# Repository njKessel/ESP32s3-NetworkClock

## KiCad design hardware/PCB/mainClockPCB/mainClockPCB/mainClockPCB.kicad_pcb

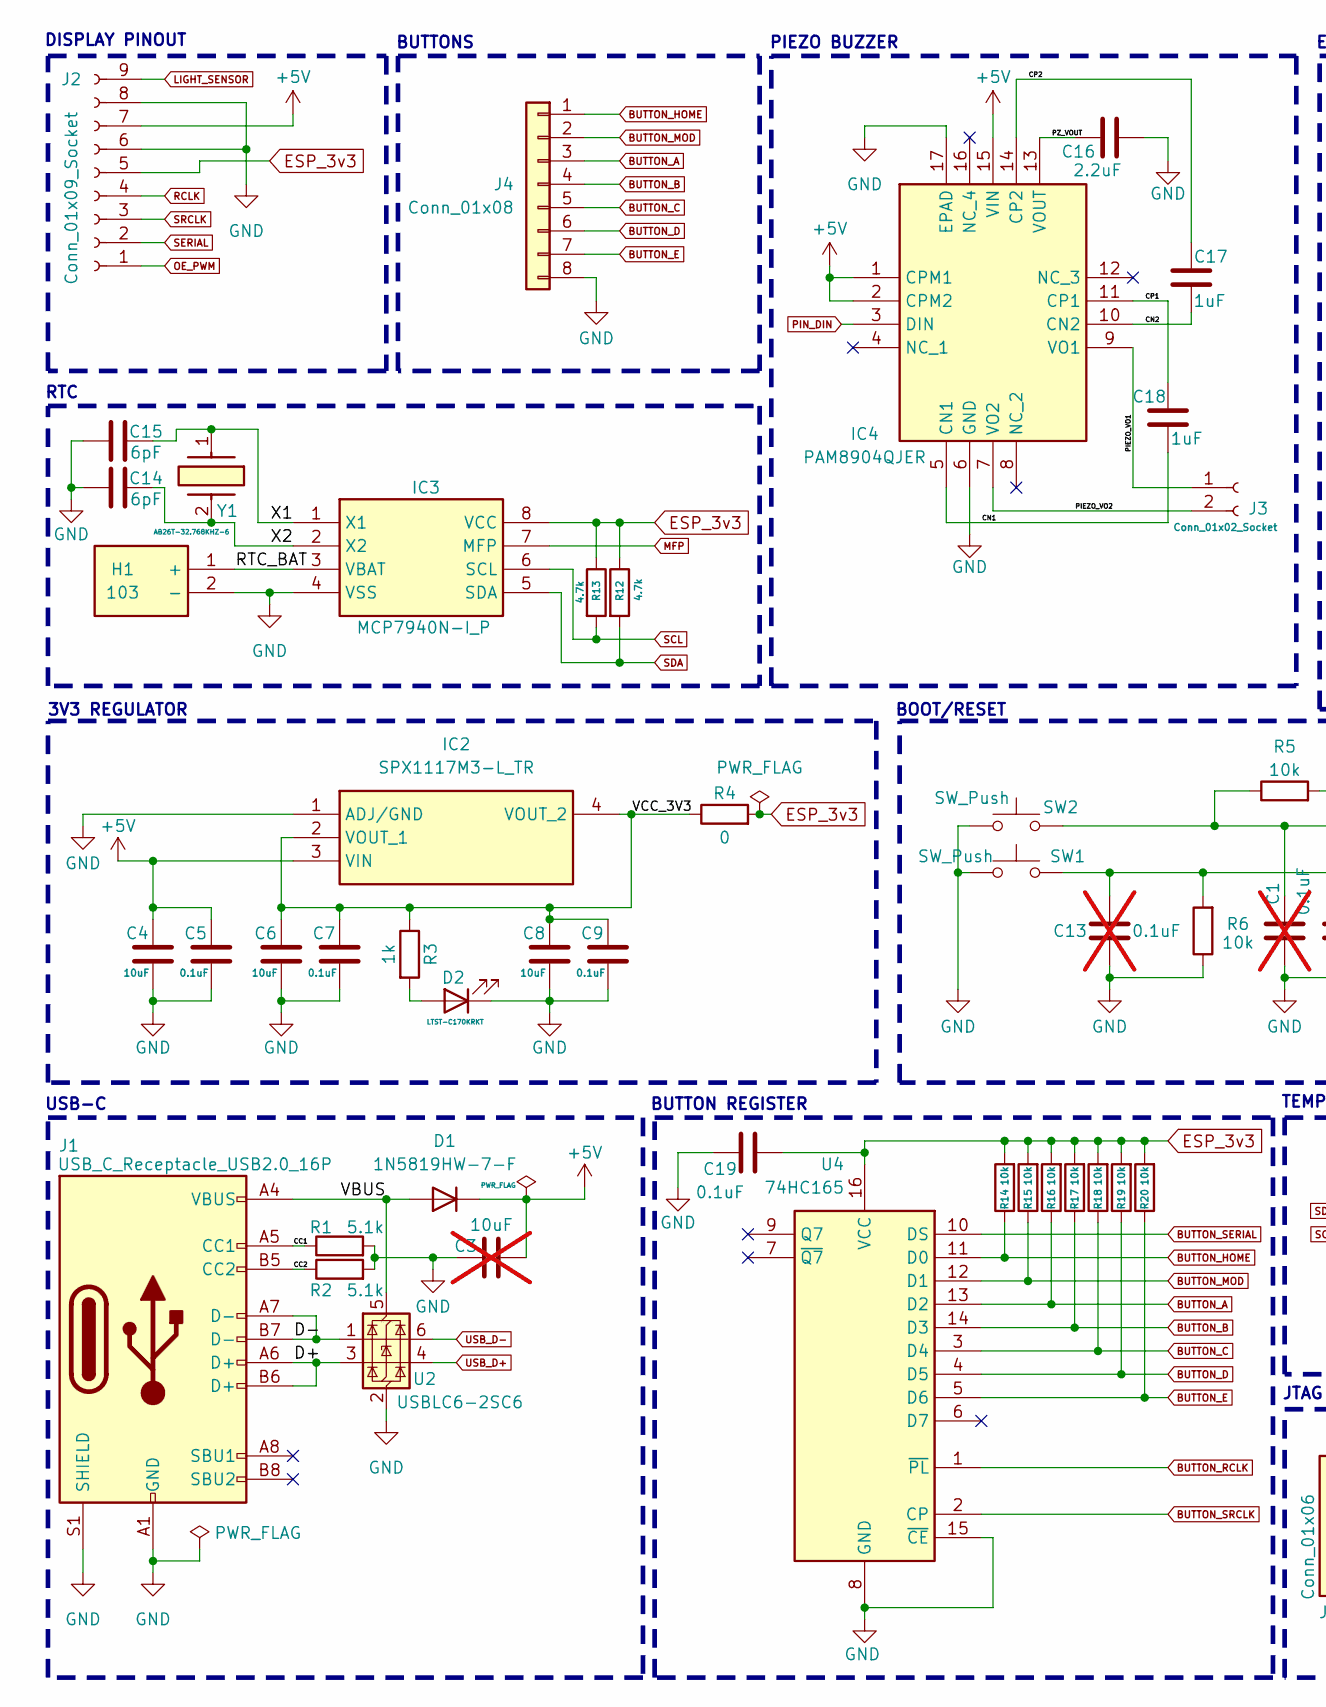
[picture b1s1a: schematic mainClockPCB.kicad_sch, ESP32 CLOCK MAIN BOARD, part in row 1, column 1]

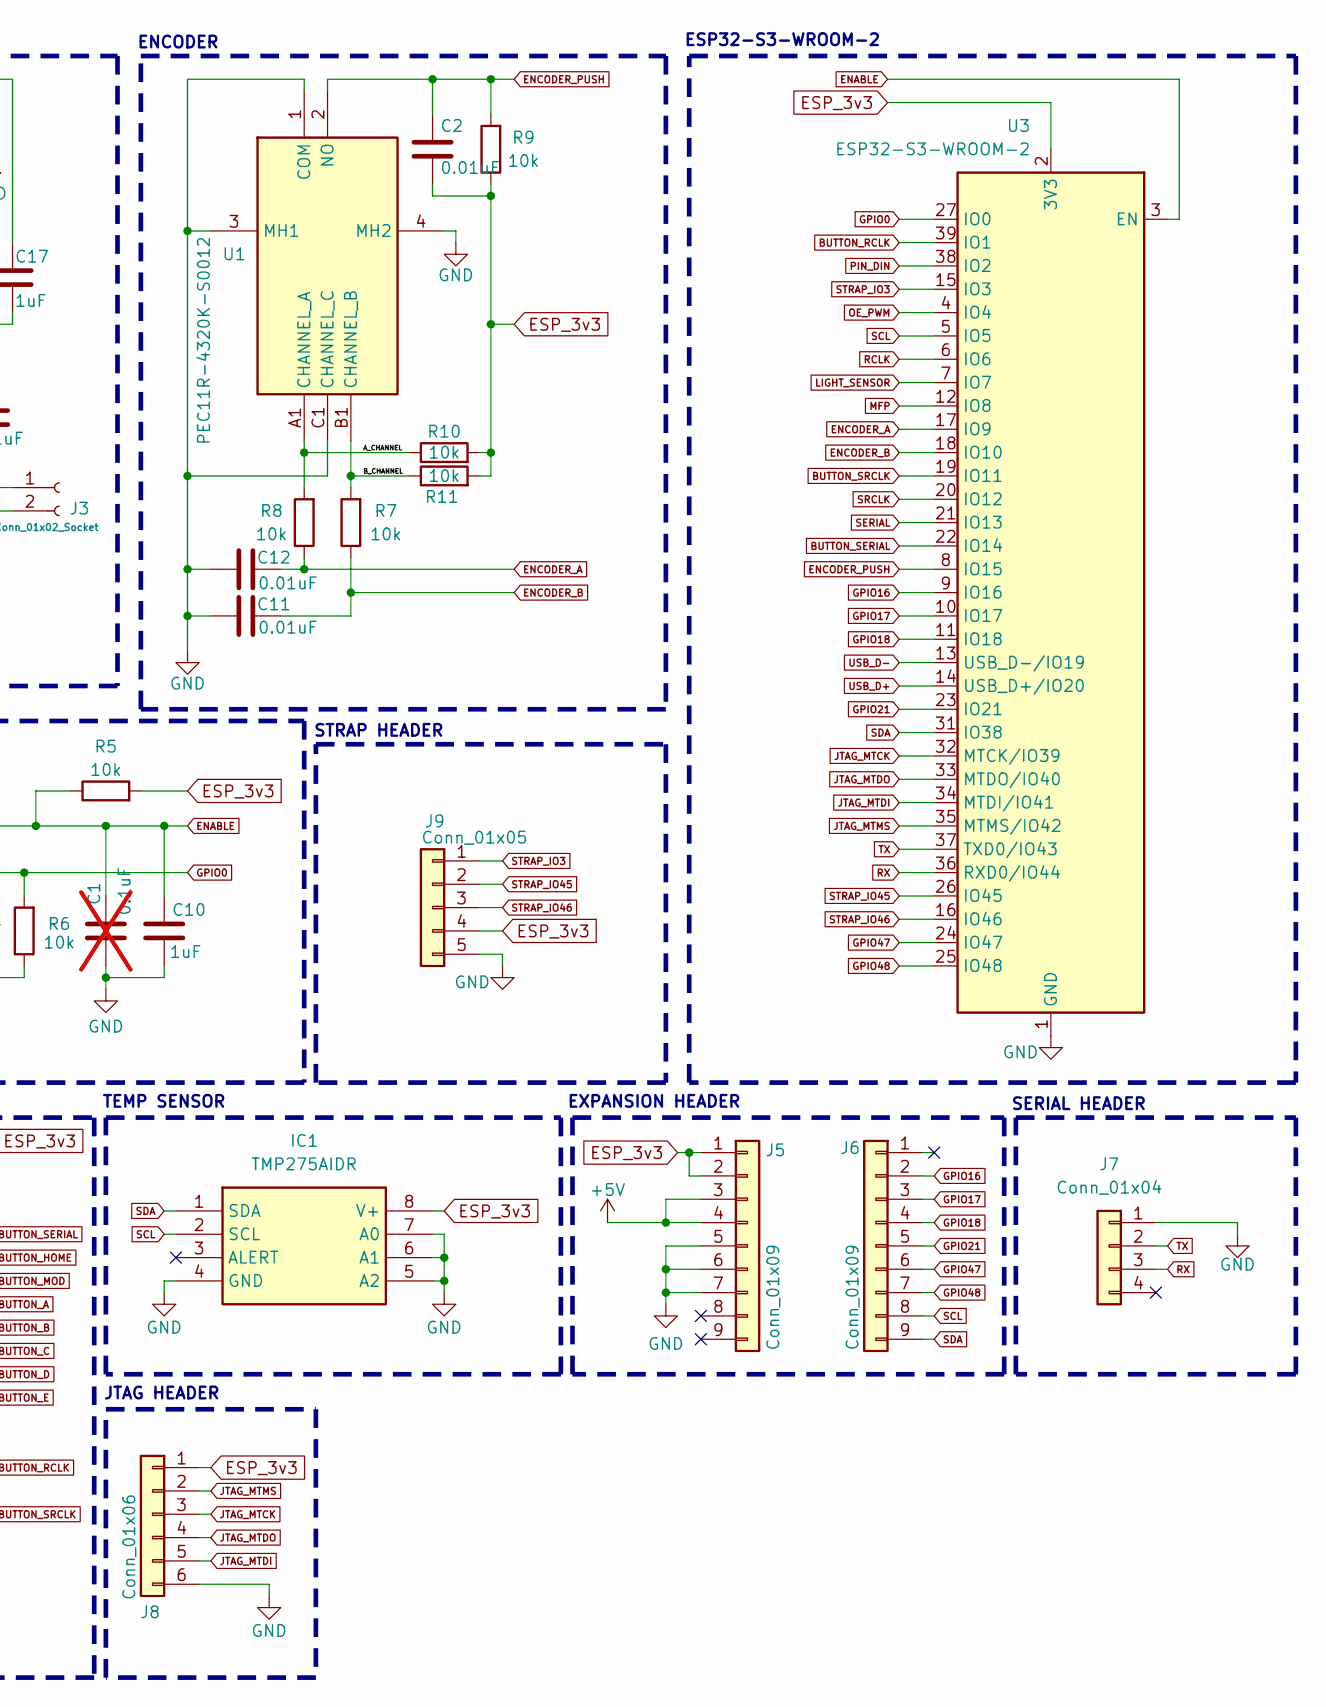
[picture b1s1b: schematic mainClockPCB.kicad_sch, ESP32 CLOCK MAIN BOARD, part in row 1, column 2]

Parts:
C1, C13: 0.1uF; C_0603_1608Metric_Pad1.08x0.95mm_HandSolder; Voltage 50V; Tolerance 10%; not fitted
C2, C11, C12: 0.01uF; C_0603_1608Metric_Pad1.08x0.95mm_HandSolder
C3: 10uF; C_0805_2012Metric_Pad1.18x1.45mm_HandSolder; not fitted
C4, C6, C8: 10uF; C_0805_2012Metric_Pad1.18x1.45mm_HandSolder
C5, C7, C9, C19: 0.1uF; C_0603_1608Metric_Pad1.08x0.95mm_HandSolder
C10, C17, C18: 1uF; C_0603_1608Metric_Pad1.08x0.95mm_HandSolder
C14, C15: 6pF; C_0603_1608Metric_Pad1.08x0.95mm_HandSolder
C16: 2.2uF; C_0603_1608Metric_Pad1.08x0.95mm_HandSolder
D1: 1N5819HW-7-F; D_SOD-123
D2: LTST-C170KRKT; LED_0805_2012Metric_Pad1.15x1.40mm_HandSolder
H1: 103; Manufacturer_Part_Number 103; Mouser Part Number 534-103
IC1: TMP275AIDR; SOIC127P600X175-8N; Manufacturer_Part_Number TMP275AIDR; Mouser Part Number 595-TMP275AIDR
IC2: SPX1117M3-L_TR; SOT230P700X180-4N; Manufacturer_Part_Number SPX1117M3-L/TR; Mouser Part Number 701-SPX1117M3-L/TR
IC3: MCP7940N-I_P; DIP781W56P254L950H533Q8N; Manufacturer_Part_Number MCP7940N-I/P; Mouser Part Number 579-MCP7940N-I/P
IC4: PAM8904QJER; QFN50P300X300X65-17N-D; Manufacturer_Part_Number PAM8904QJER; Mouser Part Number 621-PAM8904QJER
J1: USB_C_Receptacle_USB2.0_16P; USB_C_Receptacle_GCT_USB4085
J2: Conn_01x09_Socket; JST_XH_B9B-XH-A_1x09_P2.50mm_Vertical
J3: Conn_01x02_Socket; JST_XH_B2B-XH-A_1x02_P2.50mm_Vertical
J4: Conn_01x08; JST_XH_B8B-XH-A_1x08_P2.50mm_Vertical
J5, J6: Conn_01x09; PinSocket_1x09_P2.54mm_Vertical
J7: Conn_01x04; PinSocket_1x04_P2.54mm_Vertical
J8: Conn_01x06; PinSocket_1x06_P2.54mm_Vertical
J9: Conn_01x05; PinSocket_1x05_P2.54mm_Vertical
R1, R2: 5.1k; R_0603_1608Metric_Pad0.98x0.95mm_HandSolder
R3: 1k; R_0603_1608Metric_Pad0.98x0.95mm_HandSolder
R4: 0; R_0603_1608Metric_Pad0.98x0.95mm_HandSolder
R5, R6, R7, R8, R9, R10, R11, R14, R15, R16, R17, R18, R19, R20: 10k; R_0603_1608Metric_Pad0.98x0.95mm_HandSolder
R12, R13: 4.7k; R_0603_1608Metric_Pad0.98x0.95mm_HandSolder
SW1, SW2: SW_Push; SW_PUSH_6mm_H5mm
U1: PEC11R-4320K-S0012; PEC11R4320KS0012; Manufacturer_Part_Number PEC11R-4320K-S0012; Mouser Part Number 652-PEC11R-4320K-S12
U2: USBLC6-2SC6; SOT-23-6
U3: ESP32-S3-WROOM-2
U4: 74HC165; DIP-16_W7.62mm_Socket
Y1: AB26T-32.768KHZ-6; AB26T32768KHZ6; Manufacturer_Part_Number AB26T-32.768KHZ-6; Mouser Part Number 815-AB26T-32.768K-6

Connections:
+5V: C3.2, C4.1, C5.1, D1.1 (K), IC2.3 (VIN), IC4.1 (CPM1), IC4.2 (CPM2), IC4.15 (VIN), J2.7, J5.3, J5.4
/A_CHANNEL: R8.2, R10.1, U1.A1 (CHANNEL_A)
/B_CHANNEL: R7.2, R11.1, U1.B1 (CHANNEL_B)
/CC1: J1.A5 (CC1), R1.1
/CC2: J1.B5 (CC2), R2.1
/CN1: C18.1, IC4.5 (CN1)
/CN2: C17.1, IC4.10 (CN2)
/CP1: C18.2, IC4.11 (CP1)
/CP2: C17.2, IC4.14 (CP2)
/D+: J1.A6 (D+), J1.B6 (D+), U2.3 (I/O2)
/D-: J1.A7 (D-), J1.B7 (D-), U2.1 (I/O1)
/PIEZO_VO1: IC4.9 (VO1), J3.1
/PIEZO_VO2: IC4.7 (VO2), J3.2
/PZ_VOUT: C16.1, IC4.13 (VOUT)
/RTC_BAT: H1.1 (+), IC3.3 (VBAT)
/VBUS: D1.2 (A), J1.A4 (VBUS), J1.A9 (VBUS), J1.B4 (VBUS), J1.B9 (VBUS), U2.5 (VBUS)
/VCC_3V3: C6.1, C7.1, C8.1, C9.1, IC2.2 (VOUT_1), IC2.4 (VOUT_2), R3.1, R4.1
/X1: C15.2, IC3.1 (X1), Y1.1
/X2: C14.2, IC3.2 (X2), Y1.2
BUTTON_A: J4.3, R16.1, U4.13 (D2)
BUTTON_B: J4.4, R17.1, U4.14 (D3)
BUTTON_C: J4.5, R18.1, U4.3 (D4)
BUTTON_D: J4.6, R19.1, U4.4 (D5)
BUTTON_E: J4.7, R20.1, U4.5 (D6)
BUTTON_HOME: J4.1, R14.1, U4.11 (D0)
BUTTON_MOD: J4.2, R15.1, U4.12 (D1)
BUTTON_RCLK: U3.39 (IO1), U4.1 (~PL)
BUTTON_SERIAL: U3.22 (IO14), U4.10 (DS)
BUTTON_SRCLK: U3.19 (IO11), U4.2 (CP)
ENABLE: C1.1, C10.1, R5.1, SW2.2, U3.3 (EN)
ENCODER_A: C12.2, R8.1, U3.17 (IO9)
ENCODER_B: C11.1, R7.1, U3.18 (IO10)
ENCODER_PUSH: C2.1, R9.2, U1.2 (NO), U3.8 (IO15)
ESP_3v3: C2.2, C19.2, IC1.8 (V+), IC3.8 (VCC), J2.5, J5.1, J5.2, J8.1, J9.4, R4.2, R5.2, R9.1, R10.2, R11.2, R12.1, R13.1, R14.2, R15.2, R16.2, R17.2, R18.2, R19.2, R20.2, U3.2 (3V3), U4.16 (VCC)
GND: C1.2, C3.1, C4.2, C5.2, C6.2, C7.2, C8.2, C9.2, C10.2, C11.2, C12.1, C13.2, C14.1, C15.1, C16.2, C19.1, D2.1 (K), H1.2 (-), IC1.4 (GND), IC1.5 (A2), IC1.6 (A1), IC1.7 (A0), IC2.1 (ADJ/GND), IC3.4 (VSS), IC4.6 (GND), IC4.17 (EPAD), J1.A1 (GND), J1.A12 (GND), J1.B1 (GND), J1.B12 (GND), J1.S1 (SHIELD), J2.6, J2.8, J4.8, J5.5, J5.6, J5.7, J7.1, J8.6, J9.5, R1.2, R2.2, R6.1, SW1.1, SW2.1, U1.1 (COM), U1.3 (MH1), U1.4 (MH2), U1.C1 (CHANNEL_C), U2.2 (GND), U3.1 (GND), U3.40 (GND), U3.41 (GND), U4.8 (GND), U4.15 (~CE)
GPIO0: C13.1, R6.2, SW1.2, U3.27 (IO0)
GPIO16: J6.2, U3.9 (IO16)
GPIO17: J6.3, U3.10 (IO17)
GPIO18: J6.4, U3.11 (IO18)
GPIO21: J6.5, U3.23 (IO21)
GPIO47: J6.6, U3.24 (IO47)
GPIO48: J6.7, U3.25 (IO48)
JTAG_MTCK: J8.3, U3.32 (MTCK/IO39)
JTAG_MTDI: J8.5, U3.34 (MTDI/IO41)
JTAG_MTDO: J8.4, U3.33 (MTDO/IO40)
JTAG_MTMS: J8.2, U3.35 (MTMS/IO42)
LIGHT_SENSOR: J2.9, U3.7 (IO7)
MFP: IC3.7 (MFP), U3.12 (IO8)
unnamed: D2.2 (A), R3.2
OE_PWM: J2.1, U3.4 (IO4)
PIN_DIN: IC4.3 (DIN), U3.38 (IO2)
RCLK: J2.4, U3.6 (IO6)
RX: J7.3, U3.36 (RXD0/IO44)
SCL: IC1.2 (SCL), IC3.6 (SCL), J6.8, R13.2, U3.5 (IO5)
SDA: IC1.1 (SDA), IC3.5 (SDA), J6.9, R12.2, U3.31 (IO38)
SERIAL: J2.2, U3.21 (IO13)
SRCLK: J2.3, U3.20 (IO12)
STRAP_IO3: J9.1, U3.15 (IO3)
STRAP_IO45: J9.2, U3.26 (IO45)
STRAP_IO46: J9.3, U3.16 (IO46)
TX: J7.2, U3.37 (TXD0/IO43)
USB_D+: U2.4 (I/O2), U3.14 (USB_D+/IO20)
USB_D-: U2.6 (I/O1), U3.13 (USB_D-/IO19)

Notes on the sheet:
ESP32-S3-WROOM-2
TEMP SENSOR
EXPANSION HEADER
BUTTONS
BOOT/RESET
DISPLAY PINOUT
USB-C
JTAG HEADER
SERIAL HEADER
BUTTON REGISTER
3V3 REGULATOR
PIEZO BUZZER
RTC
STRAP HEADER
ENCODER

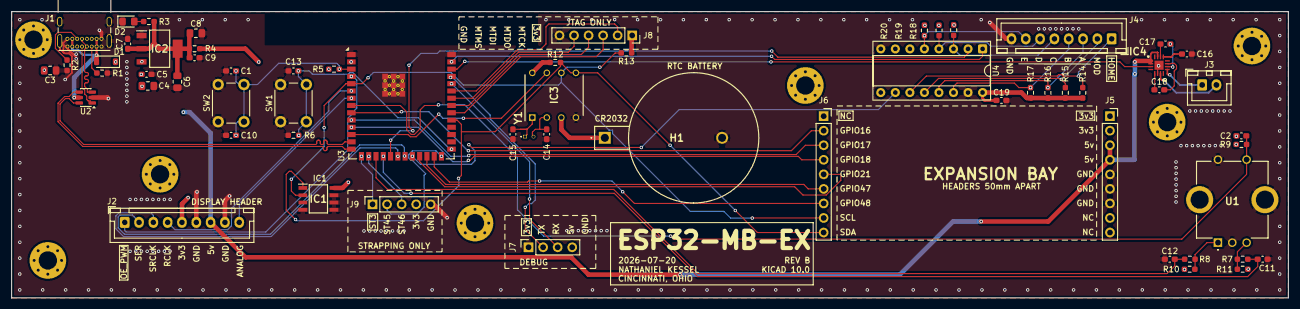
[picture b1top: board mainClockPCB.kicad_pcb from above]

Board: 4 copper layers, 223.0 x 50.0 mm, 62 parts (0 on the bottom side), 63 nets.

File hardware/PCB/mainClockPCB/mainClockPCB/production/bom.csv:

Designator,Footprint,Quantity,Value,LCSC Part #
"C10, C17, C18",0603,3,1uF,
"C11, C12, C2",0603,3,0.01uF,
"C14, C15",0603,2,6pF,
C16,0603,1,2.2uF,
"C19, C5, C7, C9",0603,4,0.1uF,
"C4, C6, C8",0805,3,10uF,
D1,D_SOD-123,1,1N5819HW-7-F,
D2,0805,1,LTST-C170KRKT,
IC1,SOIC127P600X175-8N,1,TMP275AIDR,
IC2,SOT230P700X180-4N,1,SPX1117M3-L_TR,
IC4,QFN50P300X300X65-17N-D,1,PAM8904QJER,
J2,JST_XH_B9B-XH-A_1x09_P2.50mm_Vertical,1,Conn_01x09_Socket,
J3,JST_XH_B2B-XH-A_1x02_P2.50mm_Vertical,1,Conn_01x02_Socket,
J7,PinSocket_1x04_P2.54mm_Vertical,1,Conn_01x04,
J9,PinSocket_1x05_P2.54mm_Vertical,1,Conn_01x05,
"R1, R2",0603,2,5.1k,
"R10, R11, R14, R15, R16, R17, R18, R19, R20, R5, R6, R7, R8, R9",0603,14,10k,
"R12, R13",0603,2,4.7k,
R3,0603,1,1k,
R4,0603,1,0,
U2,SOT-23-6,1,USBLC6-2SC6,
U3,ESP32-S3-WROOM-2,1,ESP32-S3-WROOM-2,

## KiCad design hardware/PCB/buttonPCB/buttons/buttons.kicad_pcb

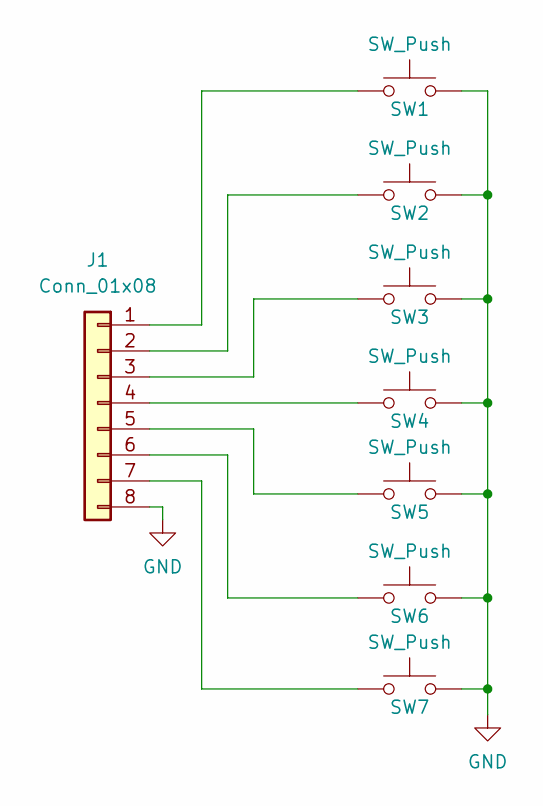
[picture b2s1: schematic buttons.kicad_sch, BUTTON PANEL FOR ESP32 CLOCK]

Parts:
J1: Conn_01x08; JST_XH_B8B-XH-A_1x08_P2.50mm_Vertical
SW1, SW2, SW3, SW4, SW5, SW6, SW7: SW_Push; SW_PUSH_6mm

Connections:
GND: J1.8, SW1.2, SW2.2, SW3.2, SW4.2, SW5.2, SW6.2, SW7.2
unnamed: J1.1, SW1.1
unnamed: J1.2, SW2.1
unnamed: J1.3, SW3.1
unnamed: J1.4, SW4.1
unnamed: J1.5, SW5.1
unnamed: J1.6, SW6.1
unnamed: J1.7, SW7.1

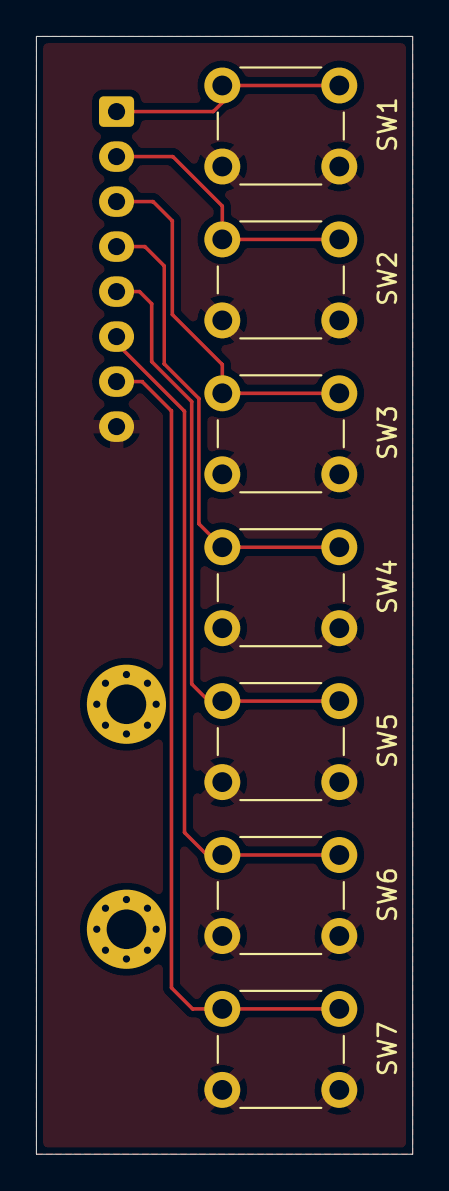
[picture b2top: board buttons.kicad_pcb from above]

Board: 2 copper layers, 20.9 x 62.1 mm, 8 parts (1 on the bottom side), 8 nets.

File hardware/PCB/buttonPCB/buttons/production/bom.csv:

Designator,Footprint,Quantity,Value,LCSC Part #
J1,JST_XH_B8B-XH-A_1x08_P2.50mm_Vertical,1,Conn_01x08,
"SW1, SW2, SW3, SW4, SW5, SW6, SW7",SW_PUSH_6mm,7,SW_Push,

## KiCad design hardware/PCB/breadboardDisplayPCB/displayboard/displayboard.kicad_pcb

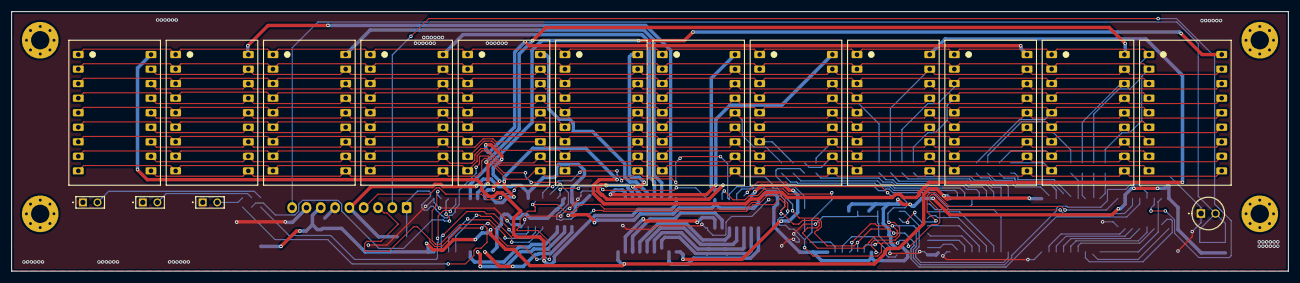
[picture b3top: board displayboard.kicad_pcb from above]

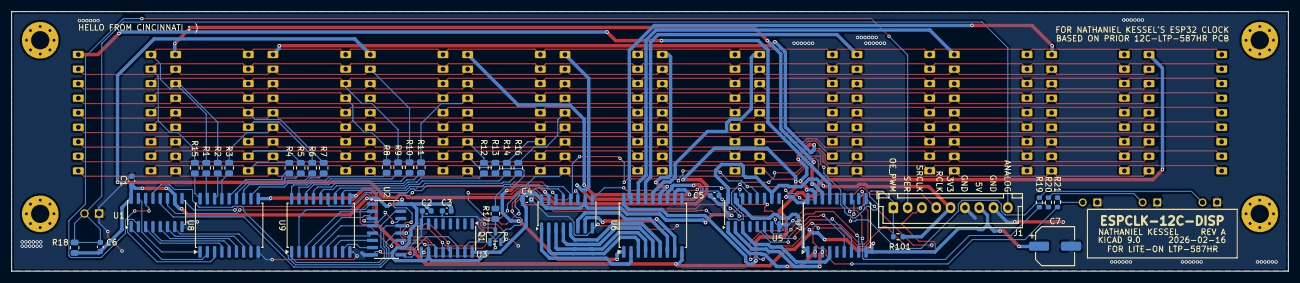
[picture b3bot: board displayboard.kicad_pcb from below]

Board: 2 copper layers, 223.0 x 45.3 mm, 56 parts (40 on the bottom side), 96 nets.

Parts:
C1, C2, C3, C4, C5, C6: 100nF; C_0603_1608Metric
C7: 47uF; CP_Elec_6.3x5.4
J1: Conn_01x09_Socket; JST_XH_B9B-XH-A_1x09_P2.50mm_Vertical
LED1, LED2, LED3: WP113IDT
LED_ALPHA1, LED_ALPHA2, LED_ALPHA3, LED_ALPHA4, LED_ALPHA5, LED_ALPHA6, LED_ALPHA7, LED_ALPHA8, LED_ALPHA9, LED_ALPHA10, LED_ALPHA11, LED_ALPHA12: LTP-587HR_DIP18
Q1: 2N7002; SOT-23
Q2: TEPT5700
R1, R2, R3, R4, R5, R6, R7, R8, R9, R10, R11, R12, R13, R14, R15, R16, R17: 100; R_0805_2012Metric
R18: 10k; R_0805_2012Metric
R19, R20, R21: 1k; R_0603_1608Metric
R101: 10k; R_0603_1608Metric
U1, U2, U3, U4, U5: 74HC595; SOIC-16_3.9x9.9mm_P1.27mm
U6, U7: TBD62783A; SOIC-18W_7.5x11.6mm_P1.27mm
U8, U9: TBD62083A; SOIC-18W_7.5x11.6mm_P1.27mm

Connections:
+3V3: C1.1, C2.2, C3.2, C4.1, C5.1, C6.1, J1.5, R18.1, R101.1, U1.10 (~SRCLR), U1.16 (VCC), U2.10 (~SRCLR), U2.16 (VCC), U3.10 (~SRCLR), U3.16 (VCC), U4.10 (~SRCLR), U4.16 (VCC), U5.10 (~SRCLR), U5.16 (VCC)
+5V: C7.1, J1.7, U6.9 (VCC), U7.9 (VCC), U8.10 (COM), U9.10 (COM)
/ANODE1: U4.15 (QA), U6.1 (I1)
/ANODE2: U4.1 (QB), U6.2 (I2)
/ANODE3: U4.2 (QC), U6.3 (I3)
/ANODE4: U4.3 (QD), U6.4 (I4)
/ANODE5: U4.4 (QE), U6.5 (I5)
/ANODE6: U4.5 (QF), U6.6 (I6)
/ANODE7: U4.6 (QG), U6.7 (I7)
/ANODE8: U4.7 (QH), U6.8 (I8)
/ANODE9: U5.15 (QA), U7.1 (I1)
/ANODE10: U5.1 (QB), U7.2 (I2)
/ANODE11: U5.2 (QC), U7.3 (I3)
/ANODE12: U5.3 (QD), U7.4 (I4)
/LED1: U5.5 (QF), U7.6 (I6)
/LED2: U5.6 (QG), U7.7 (I7)
/LED3: U5.7 (QH), U7.8 (I8)
/SEG_Ap: R15.1, U8.18 (O1)
/SEG_Asr: U1.15 (QA), U8.1 (I1)
/SEG_Bp: R1.1, U8.17 (O2)
/SEG_Bsr: U1.1 (QB), U8.2 (I2)
/SEG_Cp: R2.1, U8.16 (O3)
/SEG_Csr: U1.2 (QC), U8.3 (I3)
/SEG_DPp: Q1.3 (D), R17.1
/SEG_DPpretransistor: Q1.1 (G), U3.15 (QA)
/SEG_Dpre: R3.1, U8.15 (O4)
/SEG_Dsr: U1.3 (QD), U8.4 (I4)
/SEG_Ep: R4.1, U8.14 (O5)
/SEG_Esr: U1.4 (QE), U8.5 (I5)
/SEG_Fp: R5.1, U8.13 (O6)
/SEG_Fsr: U1.5 (QF), U8.6 (I6)
/SEG_Gp: R6.1, U8.12 (O7)
/SEG_Gsr: U1.6 (QG), U8.7 (I7)
/SEG_Hp: R7.1, U8.11 (O8)
/SEG_Hsr: U1.7 (QH), U8.8 (I8)
/SEG_Kp: R8.1, U9.18 (O1)
/SEG_Ksr: U2.15 (QA), U9.1 (I1)
/SEG_Mp: R9.1, U9.17 (O2)
/SEG_Msr: U2.1 (QB), U9.2 (I2)
/SEG_Np: R10.1, U9.16 (O3)
/SEG_Nsr: U2.2 (QC), U9.3 (I3)
/SEG_Pp: R11.1, U9.15 (O4)
/SEG_Psr: U2.3 (QD), U9.4 (I4)
/SEG_Rp: R12.1, U9.14 (O5)
/SEG_Rsr: U2.4 (QE), U9.5 (I5)
/SEG_Sp: R13.1, U9.13 (O6)
/SEG_Ssr: U2.5 (QF), U9.6 (I6)
/SEG_Tp: R14.1, U9.12 (O7)
/SEG_Tsr: U2.6 (QG), U9.7 (I7)
/SEG_Up: R16.1, U9.11 (O8)
/SEG_Usr: U2.7 (QH), U9.8 (I8)
ANALOG: C6.2, J1.9, Q2.2 (C), R18.2
ANODE1_5V: LED_ALPHA1.18 (ANODE), U6.18 (O1)
ANODE2_5V: LED_ALPHA2.18 (ANODE), U6.17 (O2)
ANODE3_5V: LED_ALPHA3.18 (ANODE), U6.16 (O3)
ANODE4_5V: LED_ALPHA4.18 (ANODE), U6.15 (O4)
ANODE5_5V: LED_ALPHA5.18 (ANODE), U6.14 (O5)
ANODE6_5V: LED_ALPHA6.18 (ANODE), U6.13 (O6)
ANODE7_5V: LED_ALPHA7.18 (ANODE), U6.12 (O7)
ANODE8_5V: LED_ALPHA8.18 (ANODE), U6.11 (O8)
ANODE9_5V: LED_ALPHA9.18 (ANODE), U7.18 (O1)
ANODE10_5V: LED_ALPHA10.18 (ANODE), U7.17 (O2)
ANODE11_5V: LED_ALPHA11.18 (ANODE), U7.16 (O3)
ANODE12_5V: LED_ALPHA12.18 (ANODE), U7.15 (O4)
ANODE_SER: U3.9 (QH'), U4.14 (SER)
GND: C1.2, C2.1, C3.1, C4.2, C5.2, C7.2, J1.6, J1.8, LED1.1 (K), LED2.1 (K), LED3.1 (K), Q1.2 (S), Q2.1 (E), U1.8 (GND), U2.8 (GND), U3.8 (GND), U4.8 (GND), U5.8 (GND), U6.10 (GND), U7.10 (GND), U8.9 (GND), U9.9 (GND)
LED1_5V: R19.1, U7.13 (O6)
LED2_5V: R20.1, U7.12 (O7)
LED3_5V: R21.1, U7.11 (O8)
unnamed: LED1.2 (A), R19.2
unnamed: LED2.2 (A), R20.2
unnamed: LED3.2 (A), R21.2
unnamed: U1.9 (QH'), U2.14 (SER)
unnamed: U2.9 (QH'), U3.14 (SER)
unnamed: U4.9 (QH'), U5.14 (SER)
OE_PWM: J1.1, R101.2, U1.13 (~OE), U2.13 (~OE), U3.13 (~OE), U4.13 (~OE), U5.13 (~OE)
RCLK: J1.4, U1.12 (RCLK), U2.12 (RCLK), U3.12 (RCLK), U4.12 (RCLK), U5.12 (RCLK)
SEG_A: LED_ALPHA1.2 (A), LED_ALPHA2.2 (A), LED_ALPHA3.2 (A), LED_ALPHA4.2 (A), LED_ALPHA5.2 (A), LED_ALPHA6.2 (A), LED_ALPHA7.2 (A), LED_ALPHA8.2 (A), LED_ALPHA9.2 (A), LED_ALPHA10.2 (A), LED_ALPHA11.2 (A), LED_ALPHA12.2 (A), R15.2
SEG_B: LED_ALPHA1.1 (B), LED_ALPHA2.1 (B), LED_ALPHA3.1 (B), LED_ALPHA4.1 (B), LED_ALPHA5.1 (B), LED_ALPHA6.1 (B), LED_ALPHA7.1 (B), LED_ALPHA8.1 (B), LED_ALPHA9.1 (B), LED_ALPHA10.1 (B), LED_ALPHA11.1 (B), LED_ALPHA12.1 (B), R1.2
SEG_C: LED_ALPHA1.16 (C), LED_ALPHA2.16 (C), LED_ALPHA3.16 (C), LED_ALPHA4.16 (C), LED_ALPHA5.16 (C), LED_ALPHA6.16 (C), LED_ALPHA7.16 (C), LED_ALPHA8.16 (C), LED_ALPHA9.16 (C), LED_ALPHA10.16 (C), LED_ALPHA11.16 (C), LED_ALPHA12.16 (C), R2.2
SEG_D: LED_ALPHA1.13 (D), LED_ALPHA2.13 (D), LED_ALPHA3.13 (D), LED_ALPHA4.13 (D), LED_ALPHA5.13 (D), LED_ALPHA6.13 (D), LED_ALPHA7.13 (D), LED_ALPHA8.13 (D), LED_ALPHA9.13 (D), LED_ALPHA10.13 (D), LED_ALPHA11.13 (D), LED_ALPHA12.13 (D), R3.2
SEG_DP: LED_ALPHA1.10 (DP), LED_ALPHA2.10 (DP), LED_ALPHA3.10 (DP), LED_ALPHA4.10 (DP), LED_ALPHA5.10 (DP), LED_ALPHA6.10 (DP), LED_ALPHA7.10 (DP), LED_ALPHA8.10 (DP), LED_ALPHA9.10 (DP), LED_ALPHA10.10 (DP), LED_ALPHA11.10 (DP), LED_ALPHA12.10 (DP), R17.2
SEG_E: LED_ALPHA1.9 (E), LED_ALPHA2.9 (E), LED_ALPHA3.9 (E), LED_ALPHA4.9 (E), LED_ALPHA5.9 (E), LED_ALPHA6.9 (E), LED_ALPHA7.9 (E), LED_ALPHA8.9 (E), LED_ALPHA9.9 (E), LED_ALPHA10.9 (E), LED_ALPHA11.9 (E), LED_ALPHA12.9 (E), R4.2
SEG_F: LED_ALPHA1.8 (F), LED_ALPHA2.8 (F), LED_ALPHA3.8 (F), LED_ALPHA4.8 (F), LED_ALPHA5.8 (F), LED_ALPHA6.8 (F), LED_ALPHA7.8 (F), LED_ALPHA8.8 (F), LED_ALPHA9.8 (F), LED_ALPHA10.8 (F), LED_ALPHA11.8 (F), LED_ALPHA12.8 (F), R5.2
SEG_G: LED_ALPHA1.6 (G), LED_ALPHA2.6 (G), LED_ALPHA3.6 (G), LED_ALPHA4.6 (G), LED_ALPHA5.6 (G), LED_ALPHA6.6 (G), LED_ALPHA7.6 (G), LED_ALPHA8.6 (G), LED_ALPHA9.6 (G), LED_ALPHA10.6 (G), LED_ALPHA11.6 (G), LED_ALPHA12.6 (G), R6.2
SEG_H: LED_ALPHA1.5 (H), LED_ALPHA2.5 (H), LED_ALPHA3.5 (H), LED_ALPHA4.5 (H), LED_ALPHA5.5 (H), LED_ALPHA6.5 (H), LED_ALPHA7.5 (H), LED_ALPHA8.5 (H), LED_ALPHA9.5 (H), LED_ALPHA10.5 (H), LED_ALPHA11.5 (H), LED_ALPHA12.5 (H), R7.2
SEG_K: LED_ALPHA1.4 (K), LED_ALPHA2.4 (K), LED_ALPHA3.4 (K), LED_ALPHA4.4 (K), LED_ALPHA5.4 (K), LED_ALPHA6.4 (K), LED_ALPHA7.4 (K), LED_ALPHA8.4 (K), LED_ALPHA9.4 (K), LED_ALPHA10.4 (K), LED_ALPHA11.4 (K), LED_ALPHA12.4 (K), R8.2
SEG_M: LED_ALPHA1.3 (M), LED_ALPHA2.3 (M), LED_ALPHA3.3 (M), LED_ALPHA4.3 (M), LED_ALPHA5.3 (M), LED_ALPHA6.3 (M), LED_ALPHA7.3 (M), LED_ALPHA8.3 (M), LED_ALPHA9.3 (M), LED_ALPHA10.3 (M), LED_ALPHA11.3 (M), LED_ALPHA12.3 (M), R9.2
SEG_N: LED_ALPHA1.17 (N), LED_ALPHA2.17 (N), LED_ALPHA3.17 (N), LED_ALPHA4.17 (N), LED_ALPHA5.17 (N), LED_ALPHA6.17 (N), LED_ALPHA7.17 (N), LED_ALPHA8.17 (N), LED_ALPHA9.17 (N), LED_ALPHA10.17 (N), LED_ALPHA11.17 (N), LED_ALPHA12.17 (N), R10.2
SEG_P: LED_ALPHA1.15, LED_ALPHA2.15, LED_ALPHA3.15, LED_ALPHA4.15, LED_ALPHA5.15, LED_ALPHA6.15, LED_ALPHA7.15, LED_ALPHA8.15, LED_ALPHA9.15, LED_ALPHA10.15, LED_ALPHA11.15, LED_ALPHA12.15, R11.2
SEG_R: LED_ALPHA1.12 (R), LED_ALPHA2.12 (R), LED_ALPHA3.12 (R), LED_ALPHA4.12 (R), LED_ALPHA5.12 (R), LED_ALPHA6.12 (R), LED_ALPHA7.12 (R), LED_ALPHA8.12 (R), LED_ALPHA9.12 (R), LED_ALPHA10.12 (R), LED_ALPHA11.12 (R), LED_ALPHA12.12 (R), R12.2
SEG_S: LED_ALPHA1.11 (S), LED_ALPHA2.11 (S), LED_ALPHA3.11 (S), LED_ALPHA4.11 (S), LED_ALPHA5.11 (S), LED_ALPHA6.11 (S), LED_ALPHA7.11 (S), LED_ALPHA8.11 (S), LED_ALPHA9.11 (S), LED_ALPHA10.11 (S), LED_ALPHA11.11 (S), LED_ALPHA12.11 (S), R13.2
SEG_T: LED_ALPHA1.7 (T), LED_ALPHA2.7 (T), LED_ALPHA3.7 (T), LED_ALPHA4.7 (T), LED_ALPHA5.7 (T), LED_ALPHA6.7 (T), LED_ALPHA7.7 (T), LED_ALPHA8.7 (T), LED_ALPHA9.7 (T), LED_ALPHA10.7 (T), LED_ALPHA11.7 (T), LED_ALPHA12.7 (T), R14.2
SEG_U: LED_ALPHA1.14 (U), LED_ALPHA2.14 (U), LED_ALPHA3.14 (U), LED_ALPHA4.14 (U), LED_ALPHA5.14 (U), LED_ALPHA6.14 (U), LED_ALPHA7.14 (U), LED_ALPHA8.14 (U), LED_ALPHA9.14 (U), LED_ALPHA10.14 (U), LED_ALPHA11.14 (U), LED_ALPHA12.14 (U), R16.2
SER: J1.2, U1.14 (SER)
SRCLK: J1.3, U1.11 (SRCLK), U2.11 (SRCLK), U3.11 (SRCLK), U4.11 (SRCLK), U5.11 (SRCLK)

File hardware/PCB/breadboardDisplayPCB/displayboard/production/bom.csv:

Designator,Footprint,Quantity,Value,LCSC Part #
"C1, C2, C3, C4, C5, C6",0603,6,100nF,C14663
C7,CP_Elec_6.3x5.4,1,47uF,C134734
Q1,SOT-23,1,2N7002,C8545
"R1, R10, R11, R12, R13, R14, R15, R16, R17, R2, R3, R4, R5, R6, R7, R8, R9",0805,17,100,C17467
R101,0603,1,10k,C25804
R18,0805,1,10k,C17414
"R19, R20, R21",0603,3,1k,C21122
"U1, U2, U3, U4, U5",SOIC-16_3.9x9.9mm_P1.27mm,5,74HC595,C14791
"U6, U7",SOIC-18W_7.5x11.6mm_P1.27mm,2,TBD62783A,C96336
"U8, U9",SOIC-18W_7.5x11.6mm_P1.27mm,2,TBD62083A,C134547

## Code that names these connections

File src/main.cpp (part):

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// PIN DEFINITIONS /////////////////////////////////////////
////////////////////////////////////////////////////////////
constexpr int PIN_COPI          =       13;               // SPI for the display
constexpr int PIN_LATCH         =       6;                // SPI RCLK for the display
constexpr int PIN_OE            =       4;                // 75HC595 display output enable, PWM control for brightness
constexpr int PIN_SCK           =       12;               // SPI clock for the display

// Peripherals /////////////////////////////////////////////
constexpr int PIN_LIGHT         =       7;                // Phototransistor
constexpr int PIN_MFP           =       8;                // External RTC 
constexpr int PIN_SCL           =       5;                // External RTC
constexpr int PIN_SDA           =       38;               // External RTC

// Encoder /////////////////////////////////////////////////
constexpr int PIN_ENCODER_PUSH  =       15;               // Encoder push button
constexpr int PIN_ENCODER_A     =       9;                // Encoder's pin A for rotation tracking
constexpr int PIN_ENCODER_B     =       10;               // Encoder's pin B for rotation tracking

// Buttons /////////////////////////////////////////////////
constexpr int PIN_COPI_BUTTON   =       14;               // SPI for the button panel
constexpr int PIN_LATCH_BUTTON  =       1;                // SPI RCLK for the button panel
constexpr int PIN_SCK_BUTTON    =       11;               // SPI clock for the button panel

////////////////////////////////////////////////////////////
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void IRAM_ATTR onTimer(void* arg) {                       // Store in internal RAM
  static uint8_t old_AB = 0;                              // init old_AB at 0 to signal no change at boot
  old_AB <<= 2;                                           // Move last check's bits over
  old_AB |= (digitalRead(PIN_ENCODER_A) << 1) | digitalRead(PIN_ENCODER_B);     
                                                          // Read the pin states and combine them to get the index for the lookup table
  old_AB &= 0x0f;                                         // Ensure max of 4 bits

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  }
  
  // Hardware Checks & Factory Reset /////////////////////////////////////////////
  pinMode(PIN_ENCODER_PUSH, INPUT);                                             // DEFINE ENCODER BUTTON AS INPUT
  if (digitalRead(PIN_ENCODER_PUSH) == LOW) {                                   // If button held on boot, wipe preferences
    Serial.println("DBG 0F0 RESET: Factory reset");
    displayBuilder(" RESETTING  ", toDisplayWords, false);
    
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
  // Display & Brightness Setup (PWM) ////////////////////////////////////////////
  pinMode(PIN_LATCH, OUTPUT);                                                   // DEFINE LATCH AS OUTPUT
  Serial.println("DBG 002 SETUP: Display latch pin.");
  
  pinMode(PIN_LIGHT, ANALOG);
  Serial.println("DBG 003 SETUP: Light sense pin.");

  const int oeChannel = 0; 
  ledcSetup(oeChannel, 5000, 8);                                                // 5kHz PWM, 8-bit resolution
  ledcAttachPin(PIN_OE, oeChannel);                                             // DEFINE OE AS OUTPUT
  Serial.println("DBG 004 SETUP: Display Output Enable Pin (Brightness).");

  setDisplayBrightness(brightnessTool.getSelectedBrightness(analogRead(PIN_LIGHT)));
  originalBrightness = brightnessTool.getSelectedBrightness(analogRead(PIN_LIGHT));
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  Serial.println("DBG 008 SETUP: Button SPI configurated");

  // Encoder & Timer Setup ///////////////////////////////////////////////////////
  pinMode(PIN_ENCODER_A, INPUT_PULLUP);                                         // DEFINE ENCODER ROTATION DETECTION
  pinMode(PIN_ENCODER_B, INPUT_PULLUP);               
  Serial.println("DBG 009 SETUP: Encoder rotation pins configured");

  setupEncoderTimer();                                                          // START TIMER FOR DEBOUNCE
  Serial.println("DBG 00A SETUP: Encoder SW Debounce configured");
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    Serial.println("DBG 000 PMINR | PER MINUTE REPORT");
    Serial.println("DBG 000 PMINR | -----------------");
    Serial.print(  "DBG 000 PMINR | UPTIME: ");           Serial.println(millis());
    Serial.print(  "DBG 000 PMINR | BRIGHTNESS: ");       Serial.println(brightnessTool.getSelectedBrightness(analogRead(PIN_LIGHT)));
    Serial.print(  "DBG 000 PMINR | WIFI: ");             Serial.println(networkTool.isConnected());
    timeSinceLastPMR = now;
  }
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    encoderMoved = false;                                                     // Reset encoder flag after capture
  }
  
  bool buttonPressed = (digitalRead(PIN_ENCODER_PUSH) == LOW);                // DETERMINE STATE OF ENCODER BUTTON

  if (buttonPressed && (now - encoderDebug_timeLastPressed > 250)) {
    Serial.println("DBG 010 INPUT: Encoder Button Detect");
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
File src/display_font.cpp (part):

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}

enum anodeBit : uint64_t {
  ANODE0 = 1ull << 24,  // 74HC595 U4 pin ANODE1 on 12C-LTP-587HR_rev1
  ANODE1 = 1ull << 25,
  ANODE2 = 1ull << 26,
  ANODE3 = 1ull << 27,
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  ANODE8 = 1ull << 32,
  ANODE9 = 1ull << 33,
  ANODE10 = 1ull << 34,
  ANODE11 = 1ull << 35, // 74HC595 U5 pin ANODE12 on 12C-LTP-587HR_rev1

  STATUS_LED1 = 1ull << 37,
  STATUS_LED2 = 1ull << 38,
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
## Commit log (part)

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2025-10-01 chore: initial commit (ESP32-S3 LCD bring-up)
2025-10-01 feat: show HH:MM:SS on line 1 and TZ on line 2 (ESP32-S3 + NTP)
2025-10-06 Rename folder to ESP32clock, refactor for clarity, update LCD code
2025-10-06 docs folder, circuit diagram for LCD, moving to 7seg LED
2025-10-06 wip: HT16K33 bring-up; wiring; Adafruit_7segment in overflow, switch to raw 8-digit next
2025-10-27 add VK16K33b test file
2025-10-27 Cleanup reset main and .gitignore encoding fix
2025-10-28 Update README.md with small desc
2025-10-28 Update README.md
    refined and expanded readme
2025-10-28 Fix formatting in README.md for clarity
    minor change
2025-10-30 Add hurdles section to README
    Added hurdles section explaining challenges with I2C and display.
2025-10-30 README formatting fix
2025-10-31 Continued work at display bitmapping, found digit maps and understanding writing digits and pointers
2025-10-31 added displaymapping reference file with traced digit bytes
2025-11-04 Built addDecimal, displayPattern array, displayIndex array, and displayTime which is incomplete.
2025-11-05 DisplayTime first working pass
2025-11-05 Final functioning LED display with circuit diagram for current clock, scope screen of SDA
2025-11-14 Time zone display mock-up
2025-11-14 Added time zone menu array for later implementation
2025-11-25 added display testing board schema and pcb (kicad pdf)
2025-11-25 Prep for alphanumeric display, made fonts header
2025-11-25 Added function displayScan and enum anodeBit for future display writing
2025-12-15 Begin of SPI display logic
2025-12-18 Worked on display logic and SPI
2025-12-30 Display solder reflow and troubleshooting, now able to display via shift regs
2025-12-31 Final screen functions and time displayed
2026-01-01 Time display formatting, shows time accurately
2026-01-01 In progress menu logic, display handling changes
2026-01-02 Reworked many functions, collapsed into a single render function, added many comments for future understanding, functioning time zone menu, fixed debounce
2026-01-06 Stopwatch Implementation
2026-01-13 RTC Microchip MCP7940N-I/P Research
2026-01-13 Redesigned display board about a week ago, will update hardware docs when board delivered
2026-01-18 Alarm design added to docs, begin alarm code/logic
2026-01-18 Update README with project hurdles and future plans
    Removed optional VFD display upgrade from future plans. Expanded on the hurdles faced in developing a custom shift-register based driver for the display modules, including details on PCB revisions an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
2026-01-20 Continued work on alarm logic
2026-01-20 Added image of clock in current state
2026-01-20 Alarm timeset display words initial logic
2026-01-22 font table format fix, add cursor, alarm edit feature begin
2026-01-22 Alarm set logic -days
2026-01-22 added kicad files to docs/hardware/PCB/breadboardDisplayPCB/displayboard/
2026-01-22 moved hardware out of docs
2026-01-23 begin of repeat alarm logic
2026-01-26 Alarm day select logic
2026-01-26 time zone menu fix
2026-01-26 moved stopwatch logic to class in stopwatch.h and stopwatch.cpp
2026-01-26 moved stopwatch classes to features folder
2026-01-26 alarm reformat, cursor reformat, stopwatch refresh rate change
2026-01-27 timezone refactor
2026-01-27 alarm save and begin functions
2026-01-27 alarm save logic
2026-01-27 alarm notification logic
2026-01-27 timer class logic
2026-01-27 timer class logic complete, edit next
2026-01-27 timerBuffer fix
2026-01-27 shouldRing logic fix
2026-01-27 timer pause fix and count fix, add timer header to main
2026-01-27 add mod and home button logic, hardware, pins
2026-01-27 timer selector debug and init fix
2026-01-27 timer countdown seconds added and debug start, removed syncing from main
    timer countdown seconds added and debug start, removed syncing from main
2026-01-27 full functioning alarm app logic
2026-01-27 Complete alarm fuction with notifications
2026-01-28 begin work on final display PCB
2026-01-29 clock h initial setup + PCB rev3 parts delivered
2026-02-01 Clock constructor, button press logic
2026-02-01 clock mod button logic
2026-02-09 final PCB rev work
2026-02-12 soldered new PCB (rev3) and corrected displayBuilder to reflect inversion of segment bits
2026-02-12 rev 3 images
2026-02-17 rev 4 PCB design finalized for display
2026-02-17 removed old main PCB file and begin on main board in mainClockPCB
2026-02-17 continue on main PCB, minor main.cpp changes for analog light sensor, RTC
2026-02-24 add home button logic to clock function
2026-02-24 time utility init commit
2026-02-24 moved time functions to time util
2026-02-24 removed time funtions from main and added timeUtil replacements
2026-02-24 functioning timeutil in main
2026-02-24 in progress clockdisplay logic
2026-02-24 PCB buzzer sound chip work
2026-02-26 clean up of display pins on main board schema
2026-02-26 clean up of USB, piezo, buttons
2026-02-26 voltage regulator schema cleanup
2026-02-26 previous commit file fix
2026-02-26 enable/boot/reset button schema cleanup
2026-02-26 encoder schema cleanup
2026-02-26 ESP32 schema cleanup
2026-02-26 button header amd PISO register
2026-02-26 expansion/debug/jtag/strap headers
2026-02-26 net label fixes
2026-02-26 power flags
2026-02-26 begin PCB design. Component layout early draft, fills, edge cuts, board setup
2026-02-26 PCB design complete
2026-02-27 initial BOM generation
2026-03-24 large commit of PCB progress
2026-03-30 added SETTINGS in menu
2026-04-14 bypass cap on PISO S
2026-04-21 KiCad 10 update, clock funtion fixes
2026-04-21 transfer clock function to clock.cpp style
2026-04-21 working focus timer
2026-04-21 brightness init
2026-04-23 Added blanking interval to render
2026-04-23 manual brightness implementation
2026-04-23 auto brightness implementation
2026-04-24 weather initial setup
2026-04-24 Revise README with project details and features
    Expanded project details, added current features, hurdles, and planned features sections.
2026-06-30 Serial header on mainboard now matches FTDI standard, JTAG changed to be more standard
2026-06-30 fixed PCB routing for JTAG and serial headers
